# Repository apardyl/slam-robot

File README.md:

# slam-robot
Software and Hardware for Kinect v2 and Odroid XU4 based mobile platform.

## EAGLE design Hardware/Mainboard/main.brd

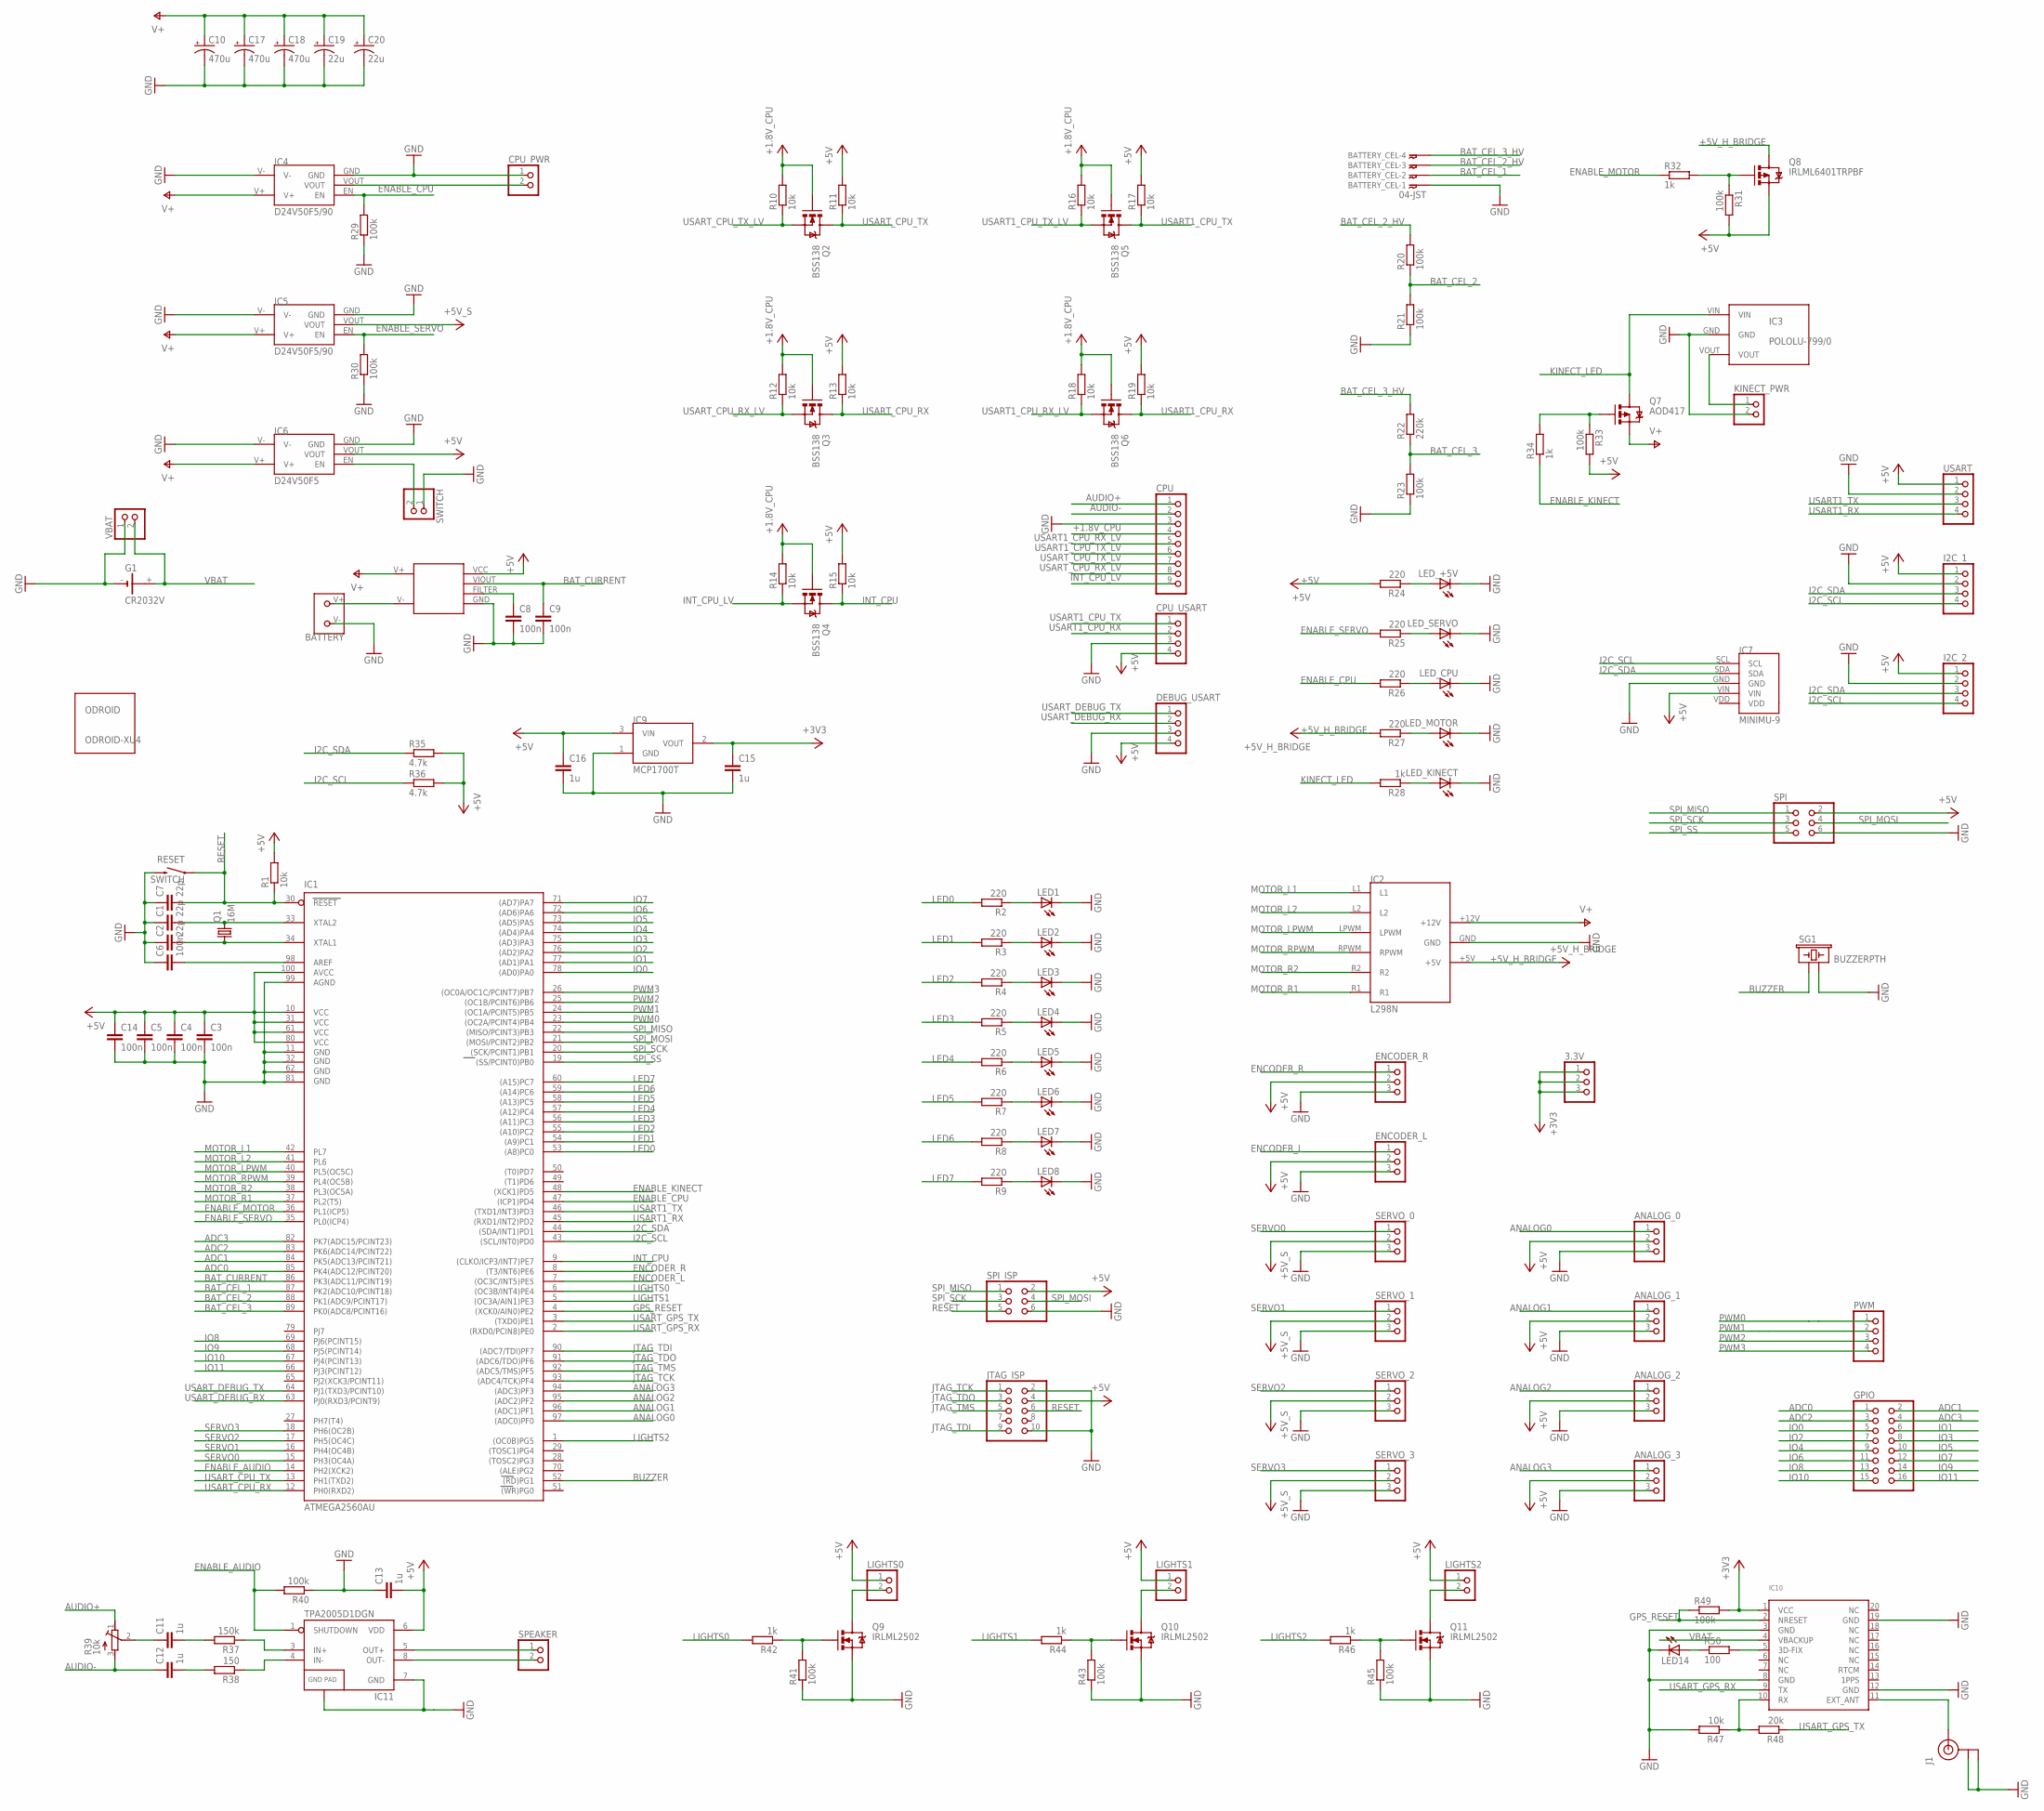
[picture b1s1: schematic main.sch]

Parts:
3.3V: PINHD-1X3; 1X03
ANALOG_0, ANALOG_1, ANALOG_2, ANALOG_3: PINHD-1X3; 1X03
BATTERY: XT60
BATTERY_CEL: 04-JST; B4B-XH
C1, C2, C7: 22p; C0805
C3, C4, C5, C6, C8, C9, C14: 100n; C0805
C10, C17, C18: 470u; PANASONIC_G
C11, C12, C13, C15, C16: 1u; C0805
C19, C20: 22u; EIA6032
CPU: PINHD-1X9; 1X09
CPU_PWR: PINHD-1X2; 1X02
CPU_USART: PINHD-1X4/90; 1X04/90
DEBUG_USART: PINHD-1X4/90; 1X04/90
ENCODER_L: PINHD-1X3; 1X03
ENCODER_R: PINHD-1X3; 1X03
G1: CR2032V
GPIO: PINHD-2X8; 2X08
I2C_1, I2C_2: PINHD-1X4; 1X04
IC1: ATMEGA2560AU; TQFP100
IC2: L298N; L298N-MOD
IC3: POLOLU-799/0; POLOLU799/0
IC4, IC5: D24V50F5/90; D24V50/90
IC6: D24V50F5; D24V50
IC7: MINIMU-9; MINIMU-9_V3
IC8: ACS715; ACS71X
IC9: MCP1700T; SOT23
IC10: GPS_FGPMMOPA6H; FGPMMOPA6H
IC11: TPA2005D1DGN; POWER-SOP8
J1: U.FL
JTAG_ISP: PINHD-2X5/90; 2X05/90
KINECT_PWR: PINHD-1X2; 1X02
LED1, LED2, LED3, LED4, LED5, LED6, LED7, LED8, LED14: LEDCHIPLED_0805; CHIPLED_0805
LED_+5V: LEDCHIPLED_0805; CHIPLED_0805
LED_CPU: LEDCHIPLED_0805; CHIPLED_0805
LED_KINECT: LEDCHIPLED_0805; CHIPLED_0805
LED_MOTOR: LEDCHIPLED_0805; CHIPLED_0805
LED_SERVO: LEDCHIPLED_0805; CHIPLED_0805
LIGHTS0, LIGHTS1, LIGHTS2: PINHD-1X2; 1X02
ODROID: ODROID-XU4
PWM: PINHD-1X4; 1X04
Q1: 16M; CRYSTAL-TXC-7A
Q2, Q3, Q4, Q5, Q6: BSS138; SOT23-3
Q7: AOD417; TO252
Q8: IRLML6401TRPBF; SOT23
Q9, Q10, Q11: IRLML2502; SOT23
R1, R10, R11, R12, R13, R14, R15, R16, R17, R18, R19, R47: 10k; R0805
R2, R3, R4, R5, R6, R7, R8, R9, R24, R25, R26, R27: 220; R0805
R20, R21, R23, R29, R30, R31, R33, R40, R41, R43, R45, R49: 100k; R0805
R22: 220k; R0805
R28, R32, R34, R42, R44, R46: 1k; R0805
R35, R36: 4.7k; R0805
R37: 150k; R0805
R38: 150; R0805
R39: 10k; RTRIM3314G
R48: 20k; R0805
R50: 100; R0805
RESET: SWITCH; TACTILE_SWITCH_TALL
SERVO_0, SERVO_1, SERVO_2, SERVO_3: PINHD-1X3; 1X03
SG1: BUZZERPTH; BUZZER-12MM
SPEAKER: PINHD-1X2; 1X02
SPI: PINHD-2X3; 2X03
SPI_ISP: PINHD-2X3; 2X03
SWITCH: PINHD-1X2/90; 1X02/90
USART: PINHD-1X4; 1X04
VBAT: PINHD-1X2; 1X02

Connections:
+1.8V_CPU: CPU.4, Q2.1 (G), Q3.1 (G), Q4.1 (G), Q5.1 (G), Q6.1 (G), R10.2, R12.2, R14.2, R16.2, R18.2
+3V3: 3.3V.1, 3.3V.2, 3.3V.3, C15.1, IC9.2 (VOUT), IC10.1 (VCC), R49.2
+5V: ANALOG_0.2, ANALOG_1.2, ANALOG_2.2, ANALOG_3.2, C3.1, C4.1, C5.1, C13.2, C14.1, C16.1, CPU_USART.4, DEBUG_USART.4, ENCODER_L.2, ENCODER_R.2, I2C_1.1, I2C_2.1, IC1.10 (VCC), IC1.31 (VCC1), IC1.61 (VCC2), IC1.80 (VCC3), IC1.100 (AVCC), IC6.VOUT, IC7.VIN, IC8.VCC, IC9.3 (VIN), IC11.6 (VDD), JTAG_ISP.4, LIGHTS0.1, LIGHTS1.1, LIGHTS2.1, Q8.2 (S), R1.2, R11.2, R13.2, R15.2, R17.2, R19.2, R24.2, R31.2, R33.2, R35.2, R36.2, SPI.2, SPI_ISP.2, USART.1
+5V_CPU: CPU_PWR.2, IC4.VOUT
+5V_H_BRIDGE: IC2.+5V, Q8.3 (D), R27.2
+5V_S: IC5.VOUT, SERVO_0.2, SERVO_1.2, SERVO_2.2, SERVO_3.2
ADC0: GPIO.1, IC1.85 (PK4(ADC12/PCINT20))
ADC1: GPIO.2, IC1.84 (PK5(ADC13/PCINT21))
ADC2: GPIO.3, IC1.83 (PK6(ADC14/PCINT22))
ADC3: GPIO.4, IC1.82 (PK7(ADC15/PCINT23))
ANALOG0: ANALOG_0.1, IC1.97 ((ADC0)PF0)
ANALOG1: ANALOG_1.1, IC1.96 ((ADC1)PF1)
ANALOG2: ANALOG_2.1, IC1.95 ((ADC2)PF2)
ANALOG3: ANALOG_3.1, IC1.94 ((ADC3)PF3)
AUDIO+: CPU.1, R39.1 (E)
AUDIO-: C12.1, CPU.2, R39.3 (A)
BAT_CEL_1: BATTERY_CEL.P$2, IC1.87 (PK2(ADC10/PCINT18))
BAT_CEL_2: IC1.88 (PK1(ADC9/PCINT17)), R20.1, R21.2
BAT_CEL_2_HV: BATTERY_CEL.P$3, R20.2
BAT_CEL_3: IC1.89 (PK0(ADC8/PCINT16)), R22.1, R23.2
BAT_CEL_3_HV: BATTERY_CEL.P$4, R22.2
BAT_CURRENT: C9.1, IC1.86 (PK3(ADC11/PCINT19)), IC8.VIOUT
BUZZER: IC1.52 ((RD)PG1), SG1.+ (1)
ENABLE: IC6.EN, SWITCH.2
ENABLE_AUDIO: IC1.14 (PH2(XCK2)), IC11.1 (SHUTDOWN), R40.2
ENABLE_CPU: IC1.47 ((ICP1)PD4), IC4.EN, R26.2, R29.2
ENABLE_KINECT: IC1.48 ((XCK1)PD5), R34.1
ENABLE_MOTOR: IC1.36 (PL1(ICP5)), R32.1
ENABLE_SERVO: IC1.35 (PL0(ICP4)), IC5.EN, R25.2, R30.2
ENCODER_L: ENCODER_L.1, IC1.7 ((OC3C/INT5)PE5)
ENCODER_R: ENCODER_R.1, IC1.8 ((T3/INT6)PE6)
GND: ANALOG_0.3, ANALOG_1.3, ANALOG_2.3, ANALOG_3.3, BATTERY.V-, BATTERY_CEL.P$1, C1.1, C2.1, C3.2, C4.2, C5.2, C6.1, C7.1, C8.2, C9.2, C10.-, C13.1, C14.2, C15.2, C16.2, C17.-, C18.-, C19.P$2 (-), C20.P$2 (-), CPU.3, CPU_PWR.1, CPU_USART.3, DEBUG_USART.3, ENCODER_L.3, ENCODER_R.3, G1.-, I2C_1.2, I2C_2.2, IC1.11 (GND), IC1.32 (GND1), IC1.62 (GND2), IC1.81 (GND3), IC1.99 (AGND), IC2.GND, IC3.GND, IC4.GND, IC4.V-, IC5.GND, IC5.V-, IC6.GND, IC6.V-, IC7.GND, IC8.GND, IC9.1 (GND), IC10.3 (GND), IC10.8 (GND), IC10.12 (GND), IC10.19 (GND), IC11.7 (GND), IC11.9 (GND), J1.P$1 (GND), J1.P$2 (GND), JTAG_ISP.2, JTAG_ISP.10, KINECT_PWR.2, LED1.C, LED2.C, LED3.C, LED4.C, LED5.C, LED6.C, LED7.C, LED8.C, LED14.C, LED_+5V.C, LED_CPU.C, LED_KINECT.C, LED_MOTOR.C, LED_SERVO.C, Q9.2 (S), Q10.2 (S), Q11.2 (S), R21.1, R23.1, R29.1, R30.1, R40.1, R41.1, R43.1, R45.1, R47.2, RESET.B2 (2), SERVO_0.3, SERVO_1.3, SERVO_2.3, SERVO_3.3, SG1.- (2), SPI.6, SPI_ISP.6, SWITCH.1, USART.2, VBAT.1
GPS_RESET: IC1.4 ((XCK0/AIN0)PE2), IC10.2 (NRESET), R49.1
I2C_SCL: I2C_1.4, I2C_2.4, IC1.43 ((SCL/INT0)PD0), IC7.SCL, R36.1
I2C_SDA: I2C_1.3, I2C_2.3, IC1.44 ((SDA/INT1)PD1), IC7.SDA, R35.1
INT_CPU: IC1.9 ((CLKO/ICP3/INT7)PE7), Q4.3 (D), R15.1
INT_CPU_LV: CPU.9, Q4.2 (S), R14.1
IO0: GPIO.5, IC1.78 ((AD0)PA0)
IO1: GPIO.6, IC1.77 ((AD1)PA1)
IO2: GPIO.7, IC1.76 ((AD2)PA2)
IO3: GPIO.8, IC1.75 ((AD3)PA3)
IO4: GPIO.9, IC1.74 ((AD4)PA4)
IO5: GPIO.10, IC1.73 ((AD5)PA5)
IO6: GPIO.11, IC1.72 ((AD6)PA6)
IO7: GPIO.12, IC1.71 ((AD7)PA7)
IO8: GPIO.13, IC1.69 (PJ6(PCINT15))
IO9: GPIO.14, IC1.68 (PJ5(PCINT14))
IO10: GPIO.15, IC1.67 (PJ4(PCINT13))
IO11: GPIO.16, IC1.66 (PJ3(PCINT12))
JTAG_TCK: IC1.93 ((ADC4/TCK)PF4), JTAG_ISP.1
JTAG_TDI: IC1.90 ((ADC7/TDI)PF7), JTAG_ISP.9
JTAG_TDO: IC1.91 ((ADC6/TDO)PF6), JTAG_ISP.3
JTAG_TMS: IC1.92 ((ADC5/TMS)PF5), JTAG_ISP.5
KINECT_LED: IC3.VIN, Q7.3 (D), R28.2
LED0: IC1.53 ((A8)PC0), R2.2
LED1: IC1.54 ((A9)PC1), R3.2
LED2: IC1.55 ((A10)PC2), R4.2
LED3: IC1.56 ((A11)PC3), R5.2
LED4: IC1.57 ((A12)PC4), R6.2
LED5: IC1.58 ((A13)PC5), R7.2
LED6: IC1.59 ((A14)PC6), R8.2
LED7: IC1.60 ((A15)PC7), R9.2
LIGHTS0: IC1.6 ((OC3B/INT4)PE4), R42.2
LIGHTS1: IC1.5 ((OC3A/AIN1)PE3), R44.2
LIGHTS2: IC1.1 ((OC0B)PG5), R46.2
MOTOR_L1: IC1.42 (PL7), IC2.L1
MOTOR_L2: IC1.41 (PL6), IC2.L2
MOTOR_LPWM: IC1.40 (PL5(OC5C)), IC2.LPWM
MOTOR_R1: IC1.37 (PL2(T5)), IC2.R1
MOTOR_R2: IC1.38 (PL3(OC5A)), IC2.R2
MOTOR_RPWM: IC1.39 (PL4(OC5B)), IC2.RPWM
unnamed: C1.2, IC1.33 (XTAL2), Q1.P$2 (2)
unnamed: C2.2, IC1.34 (XTAL1), Q1.P$1 (1)
unnamed: C6.2, IC1.98 (AREF)
unnamed: LED1.A, R2.1
unnamed: LED2.A, R3.1
unnamed: LED3.A, R4.1
unnamed: LED4.A, R5.1
unnamed: LED5.A, R6.1
unnamed: LED6.A, R7.1
unnamed: LED7.A, R8.1
unnamed: LED8.A, R9.1
unnamed: LED_+5V.A, R24.1
unnamed: BATTERY.V+, IC8.V-
unnamed: Q8.1 (G), R31.1, R32.2
unnamed: IC3.VOUT, KINECT_PWR.1
unnamed: LED_SERVO.A, R25.1
unnamed: C8.1, IC8.FILTER
unnamed: LED_CPU.A, R26.1
unnamed: LED_MOTOR.A, R27.1
unnamed: LED_KINECT.A, R28.1
unnamed: Q7.1 (G), R33.1, R34.2
unnamed: IC11.3 (IN+), R37.1
unnamed: IC11.4 (IN-), R38.1
unnamed: C11.2, R37.2
unnamed: C12.2, R38.2
unnamed: IC11.5 (OUT+), SPEAKER.1
unnamed: C11.1, R39.2 (S)
unnamed: IC11.8 (OUT-), SPEAKER.2
unnamed: LIGHTS0.2, Q9.3 (D)
unnamed: Q9.1 (G), R41.2, R42.1
unnamed: LIGHTS1.2, Q10.3 (D)
unnamed: Q10.1 (G), R43.2, R44.1
unnamed: LIGHTS2.2, Q11.3 (D)
unnamed: Q11.1 (G), R45.2, R46.1
unnamed: IC10.10 (RX), R47.1, R48.2
unnamed: IC10.5 (3D-FIX), R50.2
unnamed: LED14.A, R50.1
unnamed: IC10.11 (EXT_ANT), J1.P$3 (SIGNAL)
PWM0: IC1.23 ((OC2A/PCINT4)PB4), PWM.1
PWM1: IC1.24 ((OC1A/PCINT5)PB5), PWM.2
PWM2: IC1.25 ((OC1B/PCINT6)PB6), PWM.3
PWM3: IC1.26 ((OC0A/OC1C/PCINT7)PB7), PWM.4
RESET: C7.2, IC1.30 (RESET), JTAG_ISP.6, R1.1, RESET.A2 (1), SPI_ISP.5
SERVO0: IC1.15 (PH3(OC4A)), SERVO_0.1
SERVO1: IC1.16 (PH4(OC4B)), SERVO_1.1
SERVO2: IC1.17 (PH5(OC4C)), SERVO_2.1
SERVO3: IC1.18 (PH6(OC2B)), SERVO_3.1
SPI_MISO: IC1.22 ((MISO/PCINT3)PB3), SPI.1, SPI_ISP.1
SPI_MOSI: IC1.21 ((MOSI/PCINT2)PB2), SPI.4, SPI_ISP.4
SPI_SCK: IC1.20 ((SCK/PCINT1)PB1), SPI.3, SPI_ISP.3
SPI_SS: IC1.19 ((SS/PCINT0)PB0), SPI.5
USART1_CPU_RX: CPU_USART.2, Q6.3 (D), R19.1
USART1_CPU_RX_LV: CPU.5, Q6.2 (S), R18.1
USART1_CPU_TX: CPU_USART.1, Q5.3 (D), R17.1
USART1_CPU_TX_LV: CPU.6, Q5.2 (S), R16.1
USART1_RX: IC1.45 ((RXD1/INT2)PD2), USART.4
USART1_TX: IC1.46 ((TXD1/INT3)PD3), USART.3
USART_CPU_RX: IC1.12 (PH0(RXD2)), Q3.3 (D), R13.1
USART_CPU_RX_LV: CPU.8, Q3.2 (S), R12.1
USART_CPU_TX: IC1.13 (PH1(TXD2)), Q2.3 (D), R11.1
USART_CPU_TX_LV: CPU.7, Q2.2 (S), R10.1
USART_DEBUG_RX: DEBUG_USART.2, IC1.63 (PJ0(RXD3/PCINT9))
USART_DEBUG_TX: DEBUG_USART.1, IC1.64 (PJ1(TXD3/PCINT10))
USART_GPS_RX: IC1.2 ((RXD0/PCIN8)PE0), IC10.9 (TX)
USART_GPS_TX: IC1.3 ((TXD0)PE1), R48.1
V+: C10.+, C17.+, C18.+, C19.P$1 (+), C20.P$1 (+), IC2.+12V, IC4.V+, IC5.V+, IC6.V+, IC8.V+, Q7.2 (S)
VBAT: G1.+, IC10.4 (VBACKUP), VBAT.2

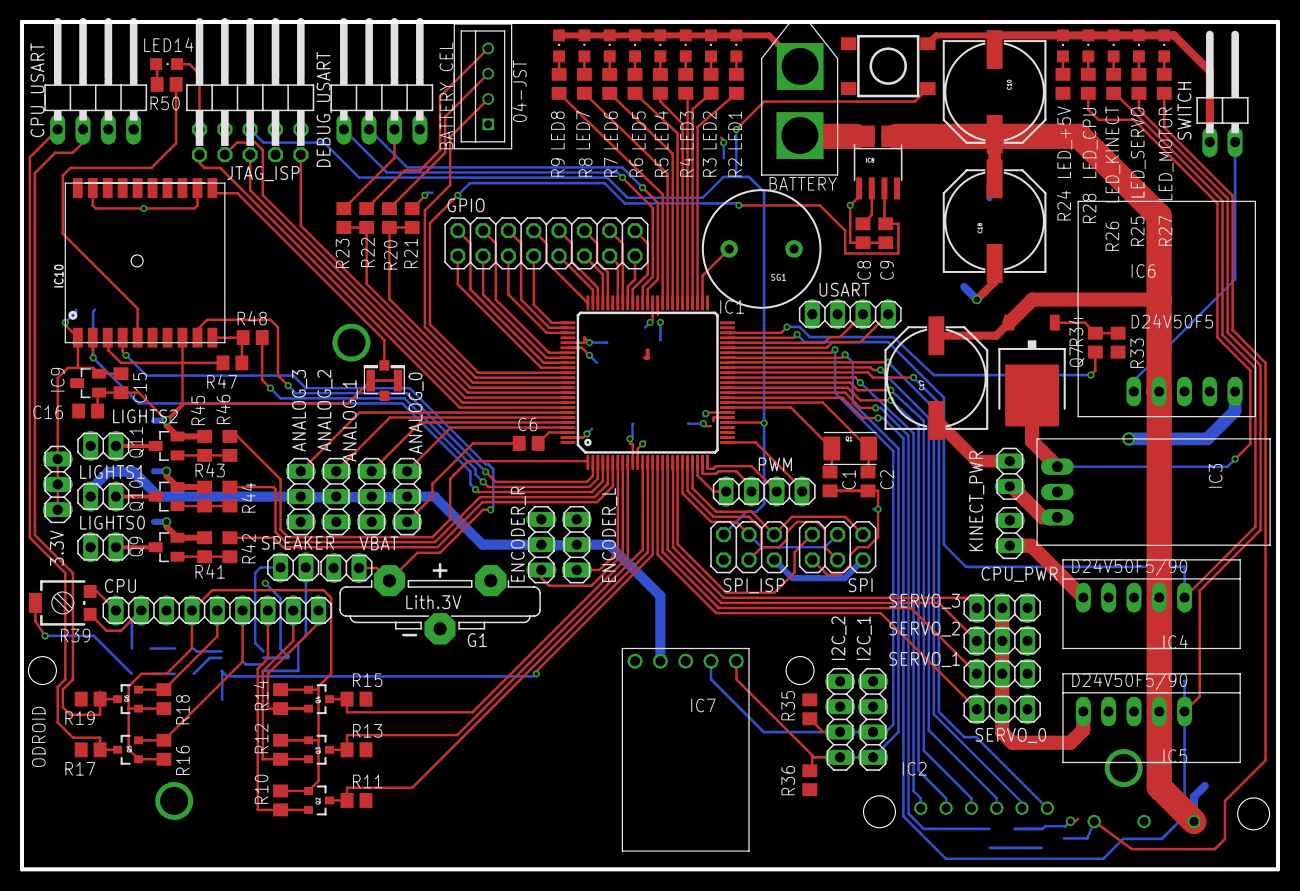
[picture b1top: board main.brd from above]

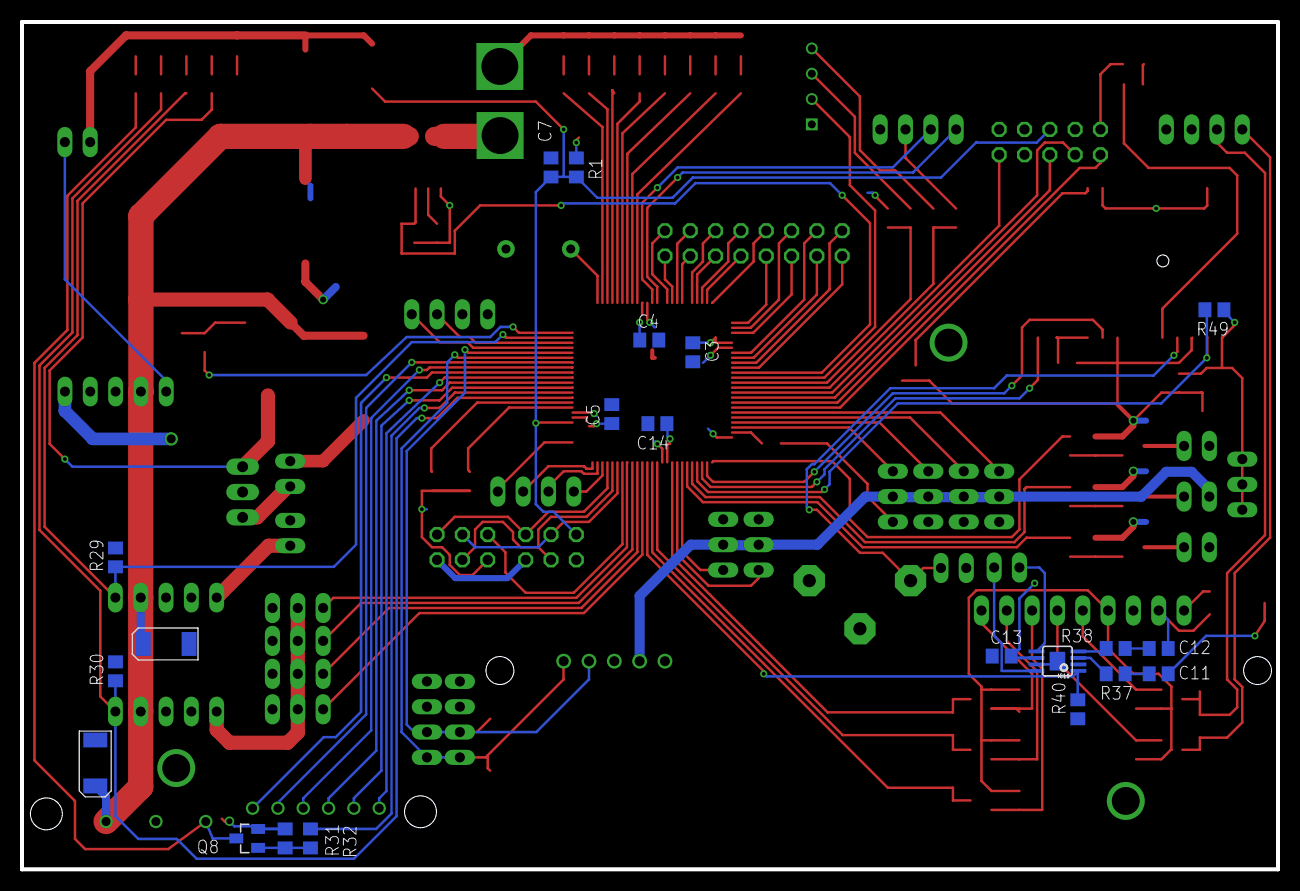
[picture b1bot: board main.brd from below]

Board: 2 copper layers, 126.0 x 85.0 mm, 143 parts (21 on the bottom side), 138 nets.

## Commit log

2016-07-07 Add mainboard design
2016-08-22 Add firmware base
2016-08-22 Add interrupt-driven I2C
2016-08-23 Add multibyte TWI transfer support
2016-09-03 Fix TWI multibyte operations, Add IMU init
2016-09-03 Add IMU read
2016-09-04 Add L3GD20H support
2016-09-04 Add sensor data transmission, Add time counter, Fix FIFO interrupt bug
2016-09-06 Add ADC, minor refactor
2016-09-11 Minor changes
2016-10-01 Add command interpreter, minor tweaks
2016-10-01 Fix i2c blocking on hardware malfunction
2017-12-27 Remove created-on-by headers, fix file endings
2017-12-27 Add AuxUSART
2017-12-27 Implement setServo and stopServo
2017-12-27 Increase max allowed motor speed
2017-12-27 Add URM37 sonar support
2017-12-27 Change motor control style
2017-12-27 Add a simple free-roam mode

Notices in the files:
parts and their libraries:
SparkFun-FreqCtrl: Licensing: Creative Commons ShareAlike 4.0 International - https://creativecommons.org/licenses/by-sa/4.0
